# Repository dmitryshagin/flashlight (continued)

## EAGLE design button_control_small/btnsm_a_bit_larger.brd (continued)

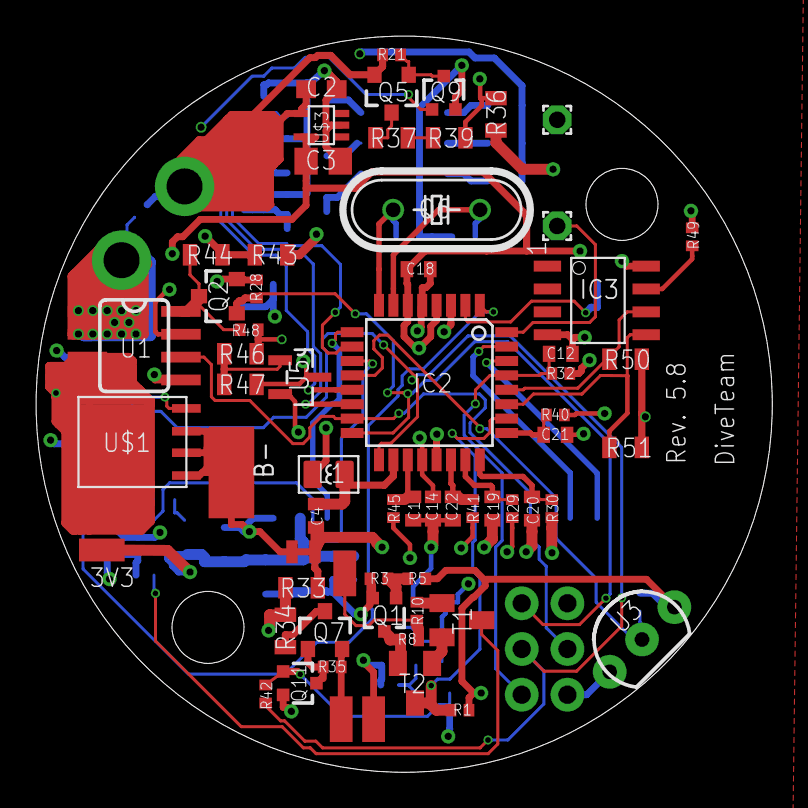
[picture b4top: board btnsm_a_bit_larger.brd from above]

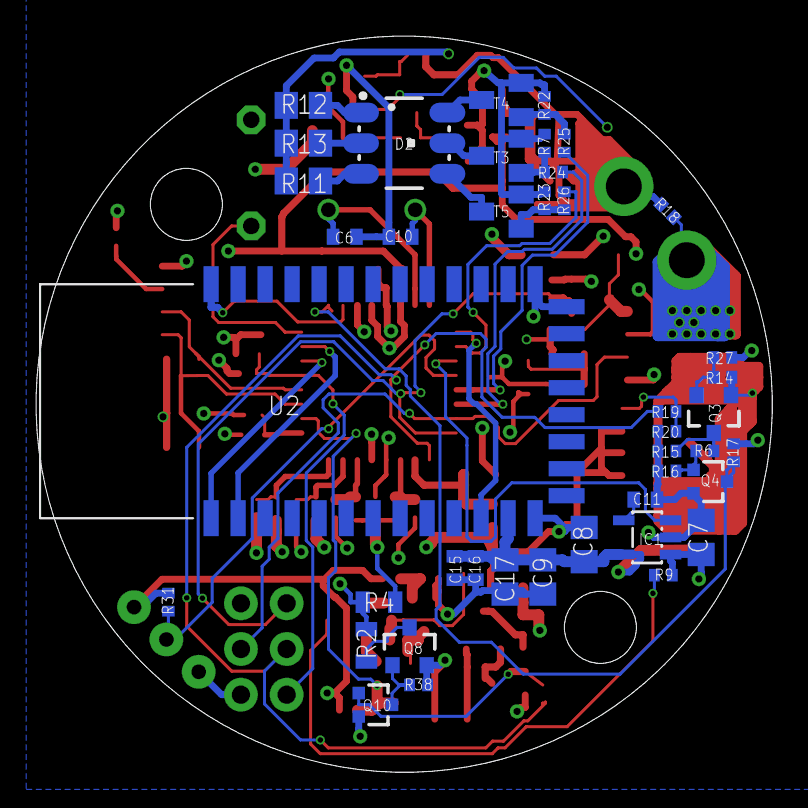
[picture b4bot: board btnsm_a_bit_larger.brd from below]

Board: 4 copper layers, 40.9 x 40.9 mm, 110 parts (42 on the bottom side), 72 nets.

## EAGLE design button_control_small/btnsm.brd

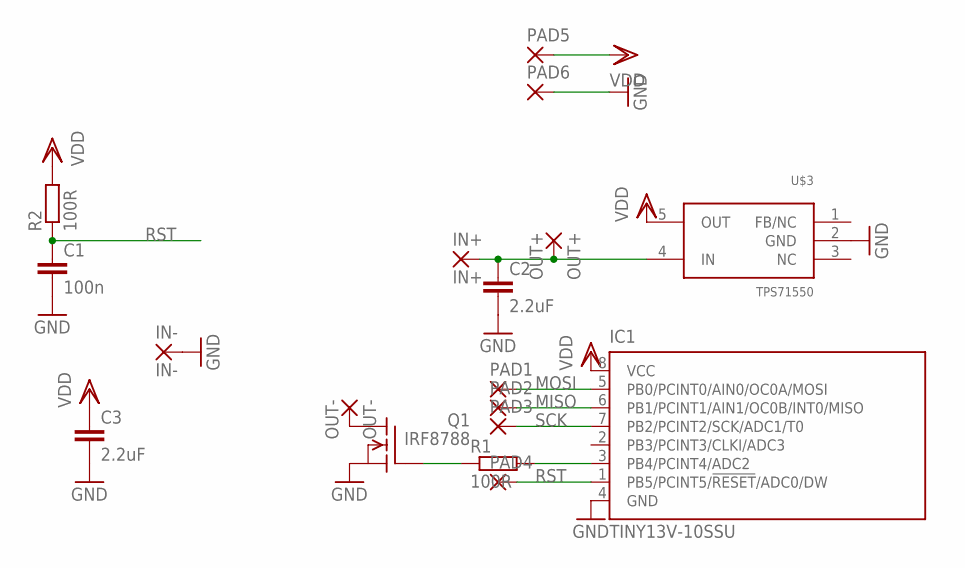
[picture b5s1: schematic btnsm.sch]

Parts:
C1: 100n; C0603
C2, C3: 2.2uF; C0603
IC1: TINY13V-10SSU; 8S1
IN+: IN+; SMD2,54-5,08
IN-: IN-; SMD2,54-5,08
OUT+: OUT+; SMD2,54-5,08
OUT-: OUT-; SMD2,54-5,08
PAD1, PAD2, PAD3, PAD4, PAD5, PAD6: 1,6/0,9
Q1: IRF8788; SO-8
R1, R2: 100R; R0402
U$3: TPS71550; SC70

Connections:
GND: C1.2, C2.2, C3.2, IC1.4 (GND), IN-.1, PAD6.1, Q1.1 (S), Q1.2 (S), Q1.3 (S), U$3.2 (GND)
MISO: IC1.6 (PB1/PCINT1/AIN1/OC0B/INT0/MISO), PAD2.1
MOSI: IC1.5 (PB0/PCINT0/AIN0/OC0A/MOSI), PAD1.1
unnamed: IC1.3 (PB4/PCINT4/ADC2), R1.2
unnamed: Q1.4 (G), R1.1
unnamed: C2.1, IN+.1, OUT+.1, U$3.4 (IN)
unnamed: OUT-.1, Q1.5 (D), Q1.6 (D), Q1.7 (D), Q1.8 (D)
RST: C1.1, IC1.1 (PB5/PCINT5/!RESET!/ADC0/DW), PAD4.1, R2.1
SCK: IC1.7 (PB2/PCINT2/SCK/ADC1/T0), PAD3.1
VDD: C3.1, IC1.8 (VCC), PAD5.1, R2.2, U$3.5 (OUT)

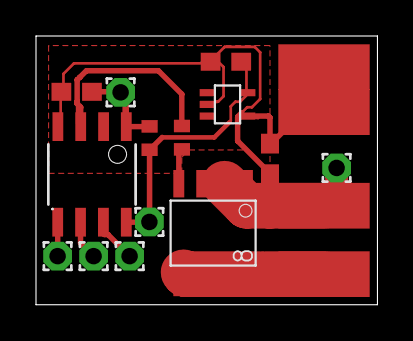
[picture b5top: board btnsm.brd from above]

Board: 2 copper layers, 19.0 x 14.9 mm, 18 parts (0 on the bottom side), 10 nets.

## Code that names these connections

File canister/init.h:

#ifndef __INIT_H__
#define __INIT_H__

#include "globals.h"
#include <avr/io.h>
#include <avr/wdt.h>
// #include "adc.h"
#include "include/ds18b20/ds18b20.h"

// Pinout:
// 1< PD3 - INT1 - Signal from external power on (active low, pulled up)
// 2> PD4 - BT_KEY - pull up to switch BT to CMD mode for HC-05. No effect for HC-06 or similar
// 3  GND
// 4  +3.3
// 5  GND
// 6  +3.3
// 7  PB6 - XTAL1 (3.6864Mhz)
// 8  PB7 - XTAL2 (3.6864Mhz)
// 9> PD5 - BT_RESET - reset if low for 5ms
// 10> PD6 - OC0A - GREEN LED
// 11> PD7 - LDO Shutdown (tie to GND for shutdown)
// 12<>PB0 - 1-Wire. DS18B20
// 13> PB1 - OC1A - BLUE LED
// 14> PB2 - OC1B - RED LED
// 15< PB3 - MOSI / input from overcurrent fault. No external pullup
// 16> PB4 - MISO / current measure output
// 17> PB5 - SCK / output - turn on output and voltage sensors
// 18  AVCC - 3.3V
// 19< ADC6 - Current measure reference
// 20  AREF - GND
// 21  GND
// 22< ADC7 - Current measure input
// 23< PC0 - Voltage measure input (12.6V)
// 24< PC1 - 8.4VIN
// 25< PC2 - 4.2VIN
// 26< PC3 - Leakage input (low => leakage present, pulled up externally)
// 27<>PC4 - SDA
// 28> PC5 - SCL
// 29< PC6 - RESET
// 30< PD0 - RX
// 31> PD1 - TX
// 32< PD2 - INT0 - button input (active low). No external pullup

#define TIMER_TUNE 		(0xFF - 144) // to get 100 Hz overflow interrrupts


#define LDO_ON 			(PORTD |=  (1 << PD7))
#define LDO_OFF			(PORTD &= ~(1 << PD7))


#define OUT_ON 			(PORTB |=  (1 << PB5))
#define OUT_OFF			(PORTB &= ~(1 << PB5))

#define MEASURE_ON  	(PORTB &= ~(1 << PB4))
#define MEASURE_OFF		(PORTB |=  (1 << PB4))

#define BT_RESET_HIGH 	(PORTD |=  (1 << PD5))
#define BT_RESET_LOW	(PORTD &= ~(1 << PD5))



void init();
void reset_wdt();

void set_LED(uint8_t R, uint8_t G, uint8_t B);

void turn_on();
void turn_off();

void process_temperature();
void process_leakage();

#endif	// _INIT_H_

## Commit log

2015-12-27 pushing flashlight project to public
2015-12-27 comments translated for pwm controller
2016-02-06 fixed adc restore
2017-07-10 Added tiny board for piezo button control
2017-09-01 Added version for heater canister
2017-12-18 Add files via upload
    Developing a new version with better power consumption and capabilities
2017-12-19 Routed version with BT module
2018-01-28 Switched to HC-05
    Added protection for water-input
    Added separate power supply for BT & DS18B20
    Added DS18B20
2018-02-17 Removed extra route, slight changes to ground poly
2018-02-17 Removed extra wire
2018-02-22 Adding low-level. Added LED & ADC.
2018-02-25 Switched to async ds18b20
2018-03-04 Changes led color, added some global statuses
2018-03-20 Added FRAM and extra capacitors
2018-04-07 Added extra ADC channels, filters to ADC & AREF
    Switched to 4 layers board in order to have proper AGND and shield ADC channels from any noise.
2018-05-29 Switched to a new hardware
2018-05-29 Bump to 5.8
2018-05-29 Added drawings
2018-08-26 Added initial BT confix, fixed power drain on powerdown
2018-11-04 Remove pullup from BT Reset on powerdown to reduce current consumption
2018-11-19 debugging rapid turn off. v01
2018-11-24 Added logging to FRAM
2018-11-25 Add realeases folder
2018-11-25 Added random software to test
2018-12-16 Added WDT & leakage recording
2018-12-16 Added UART timeout, fixed temperature output
2018-12-16 default on
2018-12-16 wdt tweak
2018-12-16 off by default
2018-12-22 Removing WDT intterrupt, adding EEPROM position saving
2018-12-25 Changes interrupts logics
2018-12-25 Interrupts rework
2018-12-25 Fixed double tap for turn on
2019-01-24 Added delay before overcurrent turn off
2019-01-24 Adding esp32 version
2019-01-26 removed overcurrent
2019-04-28 added delay to avoid pantom switching
2019-04-28 version update
